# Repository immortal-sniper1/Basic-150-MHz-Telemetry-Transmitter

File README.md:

# Basic-150-MHz-Telemetry-Transmitter      
 Basic 150MHz Telemetry Transmitter based on  https://github.com/fistlabsdev/150-MHz-Telemetry-Transmitter      

Ultra Low Power VHF-Transmitter for Wildlife Radio Tagging      
      
This Transmitter is an adaption of http://http://people.ece.cornell.edu/land/PROJECTS/TRANSMIT/.        
It has some minor changes and uses only discrete components as winding all coils etc. manually needs a lot of experienece, luck and effort to get the circuit running well and robust, which I hardly had to experience... I got two versions running stable, one manufactured in THT and one in SMD.      
      
This circuit allows to build a low-cost, tiny, light weight and very low power VHF-pulse-transmitter from scratch. It's purpose is to be used in scientific tracking applications for wildlife and livestock. This is the easiest but most effective transmitter circuit which is known to me.      
      
This circuit is operating on 150 MHz and as all radio transmitters also emitting electromagnetic waves at harmonic frequencies, so be sure that you now your local rules for the emitted frequency spectrum! This report is only a theoretical abstract so there is no legal warranty.      
      
This circuit is based on developments in the early 70s on radio telemetry for wildlife and still base for many transmitters nowadays. Check also R. Kenwards book "A manual for wildlife radio tagging" if you're interested in further information and advanced knowledge in radio tagging.      
      
The circuit is in principle a very simple single-stage oscillator based on the third harmonic of a 50MHz crystal (you can also use a different frequency crystal). Its emitting short pulses of a continuous wave signal. The pulse width and pulsing frequency is determined by a simple RC-network.
This transmitter can also be used for simple data modulation using ASK (Amplitude Shift Keying) with On-Off-Keying (OOK) by removing the components Rp and Rc and turning on/off the oscillator by applying/removing voltage (with levels Uin/GND) directly to resistor R1 (Node "EN").      

Best results were found with the following values:      
      
C1 = 100 nF      
L1 = 100 nH (In THT wind copper coil: 4x0.4mm, diameter 3mm)     
R1 = 390 kOhm     
C2 = 15 pF      
L2 = 1 µH (In THT wind copper coil: 12x0.4mm, diameter 3mm)     
NPN = MMBT3904 (In THT: 2N3904)     
XTAL = 50 MHz     
3rd harmonic determines transmitter frequency     
        
Rp = 0-1 MOhm     
Cp = 0-5 µF      
Combination of Rp and Cp determine the pulse width and Pulsing frequency.     
     
This circuit can be build on a small pcb (see also eagle schematic and layout in ".../eagle/") or directly solder the THT components to each other as a "flying assembly". As antenna you can use just a piece of copper wire with length lambda/4 which is for 150MHz: 2m/4 = 50 cm      
     
The PCB SMD version got an additional matching capacitor Cm with value 2.2pF which was added in series to the antenna.

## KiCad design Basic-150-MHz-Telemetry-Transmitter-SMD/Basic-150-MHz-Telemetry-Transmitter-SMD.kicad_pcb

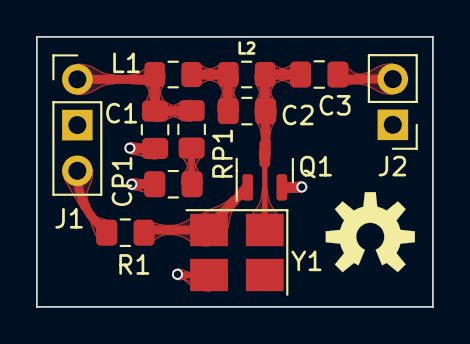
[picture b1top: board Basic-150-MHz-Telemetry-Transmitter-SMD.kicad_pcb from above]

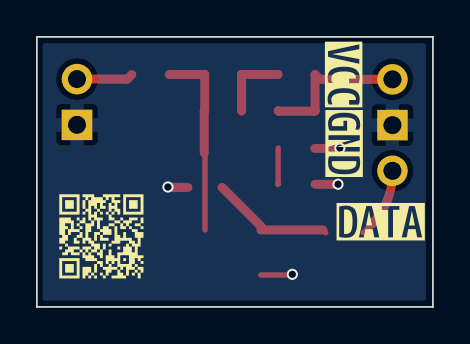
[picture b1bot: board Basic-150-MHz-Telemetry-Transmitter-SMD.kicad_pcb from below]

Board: 2 copper layers, 22.0 x 15.0 mm, 16 parts (4 on the bottom side), 8 nets.

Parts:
 : LOGO
C1, C2, C3: C_Small; C_0805_2012Metric_Pad1.18x1.45mm_HandSolder
CP1: C_Small; C_0805_2012Metric_Pad1.18x1.45mm_HandSolder
J1: input/output; PinHeader_1x03_P2.54mm_Vertical
J2: Antenna; PinHeader_1x02_P2.54mm_Vertical
L1, L2: INDUCTOR; L_0805_2012Metric_Pad1.15x1.40mm_HandSolder
Q1: MMBT3904; SOT-23
R1: R_Small; C_0805_2012Metric_Pad1.18x1.45mm_HandSolder
RP1: R_Small; C_0805_2012Metric_Pad1.18x1.45mm_HandSolder
Y1: Crystal_GND3; Crystal_SMD_SeikoEpson_FA238V-4Pin_3.2x2.5mm_HandSoldering
kibuzzard-632D4E48: G***; kibuzzard-632D4E48
kibuzzard-632D4E55: G***; kibuzzard-632D4E55
kibuzzard-632D4E64: G***; kibuzzard-632D4E64

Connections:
GND: C1.1, CP1.2, J1.2, J2.1, Q1.2 (E), Y1.3
unnamed: C1.2, J1.1, L1.1, RP1.1
unnamed: C2.1, C3.1, L2.2, Q1.3 (C), Y1.1
unnamed: C2.2, L1.2, L2.1
unnamed: CP1.1, RP1.2
unnamed: C3.2, J2.2
unnamed: Q1.1 (B), R1.2, Y1.2
data: J1.3, R1.1

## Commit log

2022-07-11 smd ver
2022-10-05 fixes
